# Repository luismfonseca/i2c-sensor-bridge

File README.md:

# I2C Sensor Bridge

These are mostly Arduino-like, with a square-form factor, without usb interface but with a mini breadboard built-in.
They also expose 4 I2C interfaces so they can be daisy-chained.

## ATtiny84 version

## ATmega328p version

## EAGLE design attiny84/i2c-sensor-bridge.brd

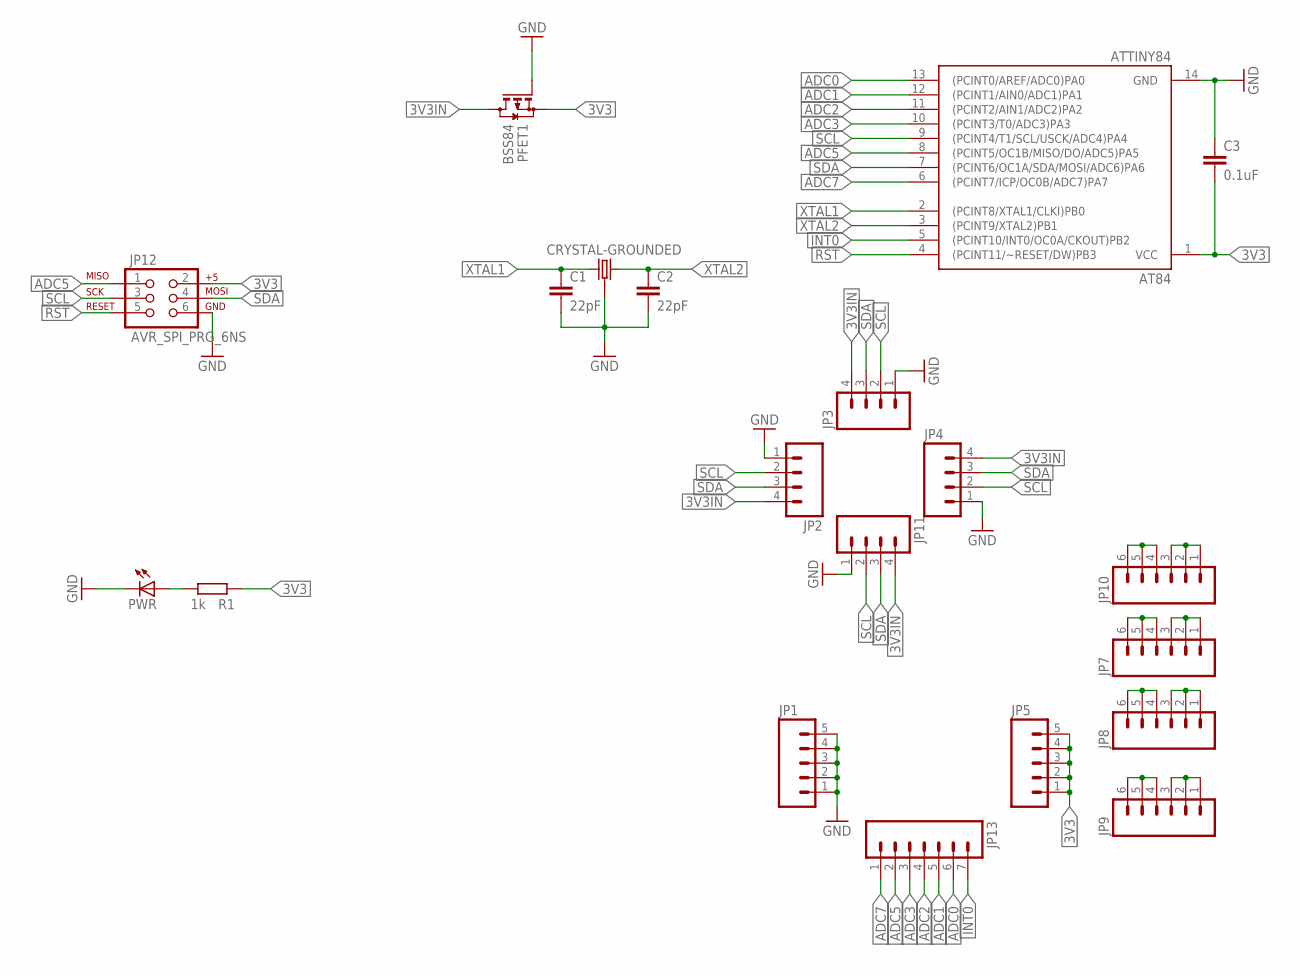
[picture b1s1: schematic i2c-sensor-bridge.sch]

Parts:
AT84: ATTINY84; SO14
C1, C2: 22pF; C0805
C3: 0.1uF; C0805
CRYSTAL: CRYSTAL-GROUNDED; CRYSTAL-SMD-5X3
JP1, JP5: M05LOCK; 1X05_LOCK
JP2, JP3, JP4, JP11: M04LOCK; 1X04_LOCK
JP7, JP8, JP9, JP10: M06NO_SILK_FEMALE_PTH; 1X06_NO_SILK
JP12: AVR_SPI_PRG_6NS; 2X3-NS
JP13: M07LOCK; 1X07_LOCK
PFET1: BSS84; SOT23
PWR: LEDCHIPLED_0805; CHIPLED_0805
R1: 1k; R0805

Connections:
3V3: AT84.1 (VCC), C3.2, JP5.1, JP5.2, JP5.3, JP5.4, JP5.5, JP12.2, PFET1.2 (S), R1.2
3V3IN: JP2.4, JP3.4, JP4.4, JP11.4, PFET1.3 (D)
ADC0: AT84.13 ((PCINT0/AREF/ADC0)PA0), JP13.6
ADC1: AT84.12 ((PCINT1/AIN0/ADC1)PA1), JP13.5
ADC2: AT84.11 ((PCINT2/AIN1/ADC2)PA2), JP13.4
ADC3: AT84.10 ((PCINT3/T0/ADC3)PA3), JP13.3
ADC5: AT84.8 ((PCINT5/OC1B/MISO/DO/ADC5)PA5), JP12.1, JP13.2
ADC7: AT84.6 ((PCINT7/ICP/OC0B/ADC7)PA7), JP13.1
GND: AT84.14 (GND), C1.2, C2.2, C3.1, CRYSTAL.2 (3), CRYSTAL.4 (3), JP1.1, JP1.2, JP1.3, JP1.4, JP1.5, JP2.1, JP3.1, JP4.1, JP11.1, JP12.6, PFET1.1 (G), PWR.C
INT0: AT84.5 ((PCINT10/INT0/OC0A/CKOUT)PB2), JP13.7
unnamed: PWR.A, R1.1
unnamed: JP10.4, JP10.5, JP10.6
unnamed: JP10.1, JP10.2, JP10.3
unnamed: JP7.1, JP7.2, JP7.3
unnamed: JP7.4, JP7.5, JP7.6
unnamed: JP8.4, JP8.5, JP8.6
unnamed: JP8.1, JP8.2, JP8.3
unnamed: JP9.1, JP9.2, JP9.3
unnamed: JP9.4, JP9.5, JP9.6
RST: AT84.4 ((PCINT11/~RESET/DW)PB3), JP12.5
SCL: AT84.9 ((PCINT4/T1/SCL/USCK/ADC4)PA4), JP2.2, JP3.2, JP4.2, JP11.2, JP12.3
SDA: AT84.7 ((PCINT6/OC1A/SDA/MOSI/ADC6)PA6), JP2.3, JP3.3, JP4.3, JP11.3, JP12.4
XTAL1: AT84.2 ((PCINT8/XTAL1/CLKI)PB0), C1.1, CRYSTAL.3 (1)
XTAL2: AT84.3 ((PCINT9/XTAL2)PB1), C2.1, CRYSTAL.1 (2)

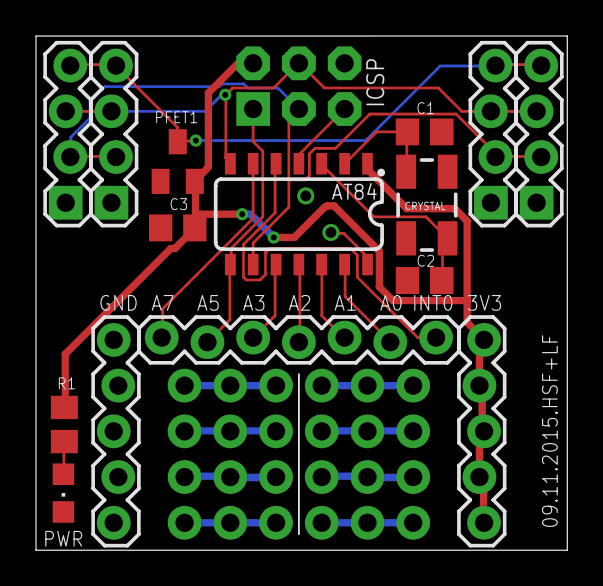
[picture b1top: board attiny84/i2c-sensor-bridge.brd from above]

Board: 2 copper layers, 29.5 x 28.6 mm, 20 parts (0 on the bottom side), 24 nets.

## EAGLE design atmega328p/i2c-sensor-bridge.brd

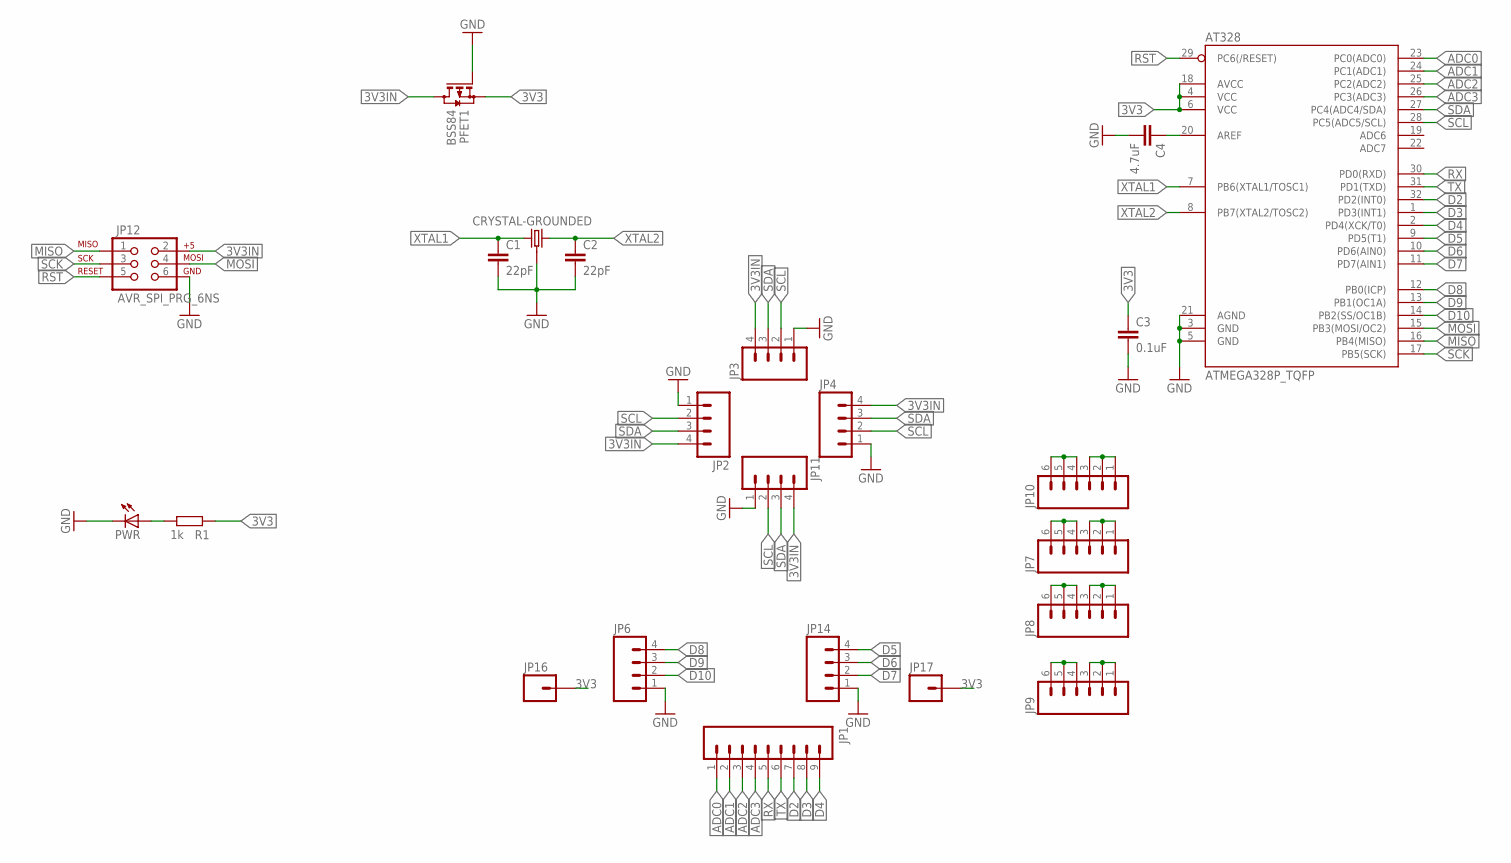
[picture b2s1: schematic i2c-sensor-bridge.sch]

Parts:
AT328: ATMEGA328P_TQFP; TQFP32-08
C1, C2: 22pF; C0805
C3: 0.1uF; C0805
C4: 4.7uF; C0805
CRYSTAL: CRYSTAL-GROUNDED; CRYSTAL-SMD-5X3
JP1: M09LOCK; 1X09_LOCK
JP2, JP3, JP4, JP6, JP11, JP14: M04LOCK; 1X04_LOCK
JP7, JP8, JP9, JP10: M06NO_SILK_FEMALE_PTH; 1X06_NO_SILK
JP12: AVR_SPI_PRG_6NS; 2X3-NS
JP16, JP17: M01PTH_NO_SILK_YES_STOP; 1X01_NO_SILK
PFET1: BSS84; SOT23
PWR: LEDCHIPLED_0805; CHIPLED_0805
R1: 1k; R0805

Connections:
3V3: AT328.4 (VCC), AT328.6 (VCC), AT328.18 (AVCC), C3.1, JP16.1, JP17.1, PFET1.2 (S), R1.2
3V3IN: JP2.4, JP3.4, JP4.4, JP11.4, JP12.2, PFET1.3 (D)
ADC0: AT328.23 (PC0(ADC0)), JP1.1
ADC1: AT328.24 (PC1(ADC1)), JP1.2
ADC2: AT328.25 (PC2(ADC2)), JP1.3
ADC3: AT328.26 (PC3(ADC3)), JP1.4
D2: AT328.32 (PD2(INT0)), JP1.7
D3: AT328.1 (PD3(INT1)), JP1.8
D4: AT328.2 (PD4(XCK/T0)), JP1.9
D5: AT328.9 (PD5(T1)), JP14.4
D6: AT328.10 (PD6(AIN0)), JP14.3
D7: AT328.11 (PD7(AIN1)), JP14.2
D8: AT328.12 (PB0(ICP)), JP6.4
D9: AT328.13 (PB1(OC1A)), JP6.3
D10: AT328.14 (PB2(SS/OC1B)), JP6.2
GND: AT328.3 (GND), AT328.5 (GND), AT328.21 (AGND), C1.2, C2.2, C3.2, C4.2, CRYSTAL.2 (3), CRYSTAL.4 (3), JP2.1, JP3.1, JP4.1, JP6.1, JP11.1, JP12.6, JP14.1, PFET1.1 (G), PWR.C
MISO: AT328.16 (PB4(MISO)), JP12.1
MOSI: AT328.15 (PB3(MOSI/OC2)), JP12.4
unnamed: PWR.A, R1.1
unnamed: JP10.4, JP10.5, JP10.6
unnamed: JP10.1, JP10.2, JP10.3
unnamed: JP7.1, JP7.2, JP7.3
unnamed: JP7.4, JP7.5, JP7.6
unnamed: JP8.4, JP8.5, JP8.6
unnamed: JP8.1, JP8.2, JP8.3
unnamed: JP9.1, JP9.2, JP9.3
unnamed: JP9.4, JP9.5, JP9.6
unnamed: AT328.20 (AREF), C4.1
RST: AT328.29 (PC6(/RESET)), JP12.5
RX: AT328.30 (PD0(RXD)), JP1.5
SCK: AT328.17 (PB5(SCK)), JP12.3
SCL: AT328.28 (PC5(ADC5/SCL)), JP2.2, JP3.2, JP4.2, JP11.2
SDA: AT328.27 (PC4(ADC4/SDA)), JP2.3, JP3.3, JP4.3, JP11.3
TX: AT328.31 (PD1(TXD)), JP1.6
XTAL1: AT328.7 (PB6(XTAL1/TOSC1)), C1.1, CRYSTAL.3 (1)
XTAL2: AT328.8 (PB7(XTAL2/TOSC2)), C2.1, CRYSTAL.1 (2)

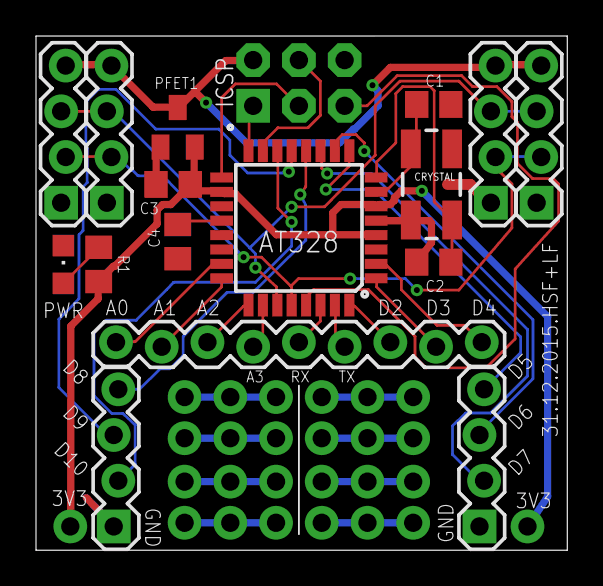
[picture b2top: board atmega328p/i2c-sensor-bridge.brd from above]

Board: 2 copper layers, 29.5 x 28.6 mm, 23 parts (0 on the bottom side), 36 nets.

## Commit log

2015-11-10 Initial version of the I2C sensor bridge
2016-02-03 Add a breadboard for the ATmega328p chip
2016-02-03 Move ATTiny84 to it's folder
2016-02-03 Add ATmega328 images and datasheet

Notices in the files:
parts and their libraries:
SparkFun-Connectors: Licensing: Creative Commons ShareAlike 4.0 International - https://creativecommons.org/licenses/by-sa/4.0
